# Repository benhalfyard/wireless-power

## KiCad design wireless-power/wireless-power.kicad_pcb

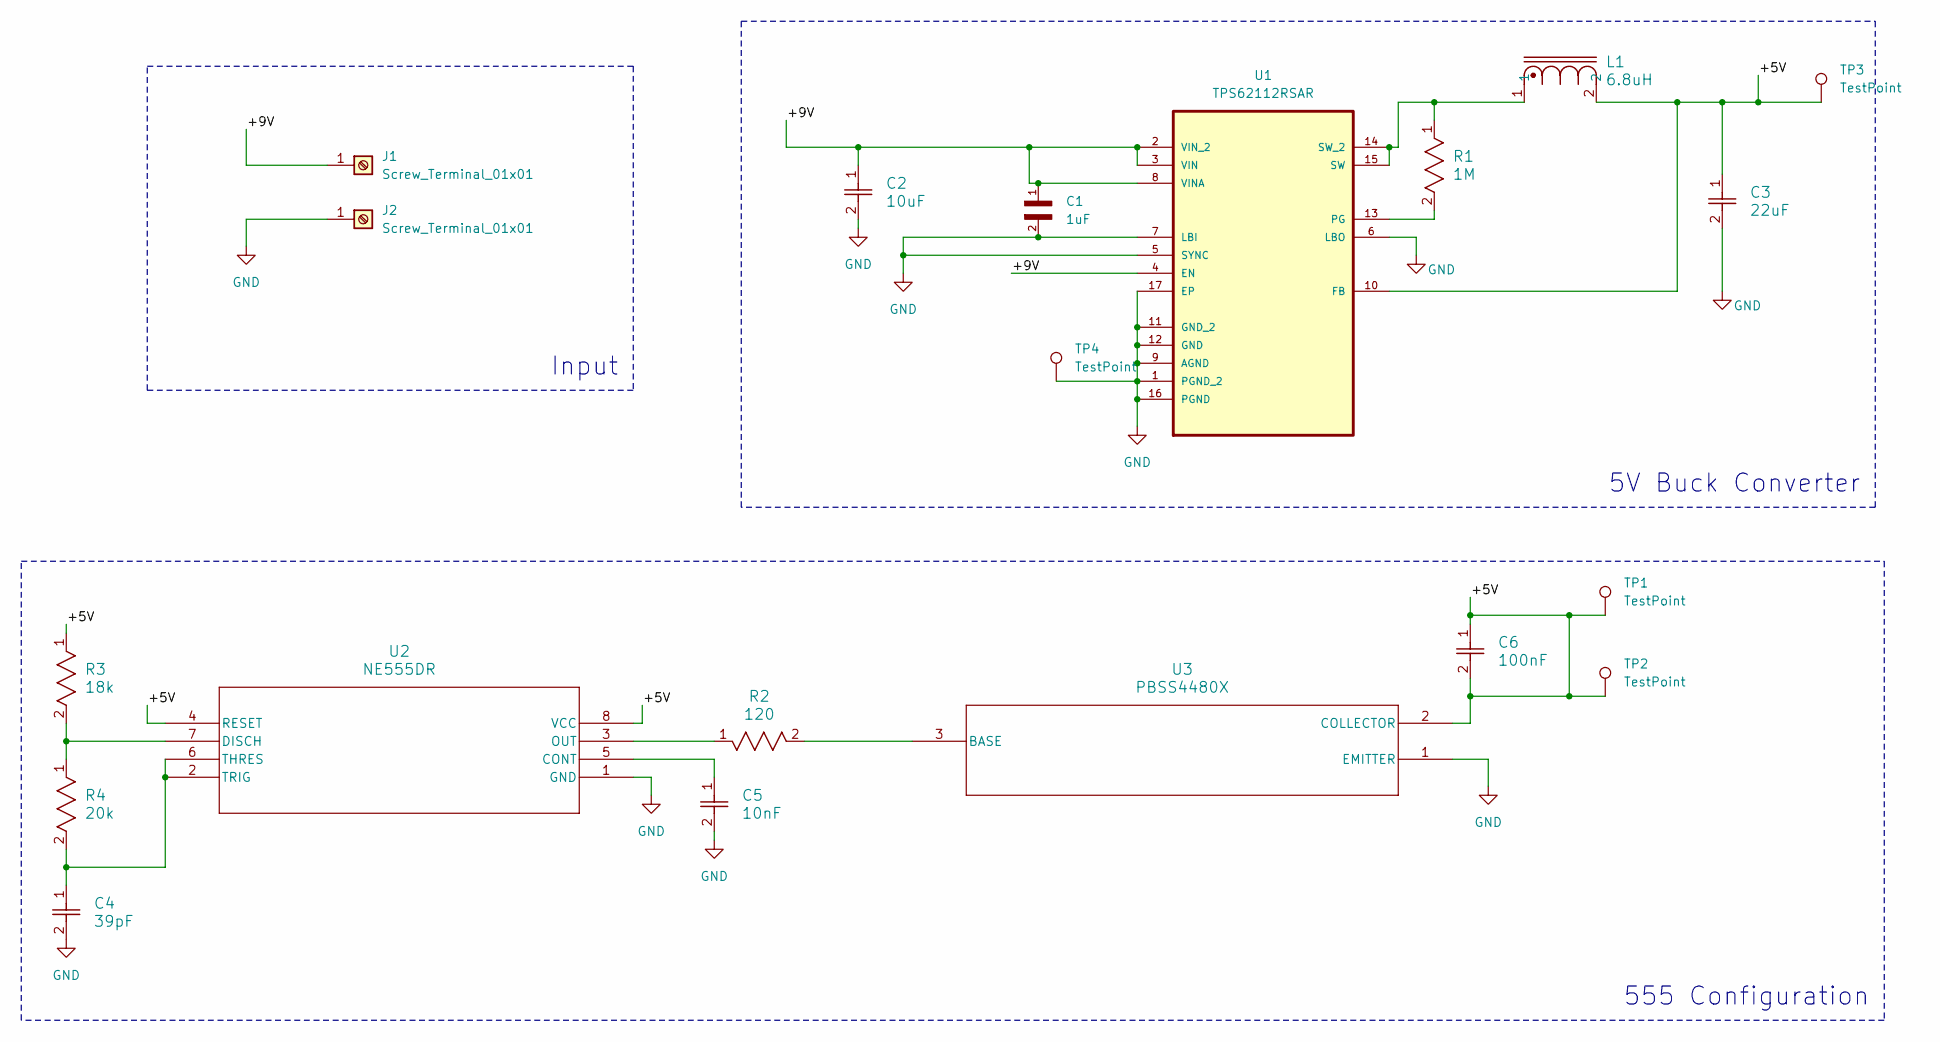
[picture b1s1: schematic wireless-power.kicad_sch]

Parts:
C1: 1uF; CAPC2012X135N
C2: 10uF; CAP_C3225-250_TDK
C3: 22uF; CAP_C3225-250_TDK
C4: 39pF; CAPC6333_33N_KEM
C5: 10nF; G-155_MUR
C6: 100nF; G-033_MUR
J1, J2: Screw_Terminal_01x01; TestPoint_Keystone_5019_Minature
L1: 6.8uH; DR125
R1: 1M; RC0603N_YAG
R2: 120; RC0603N_PAN
R3: 18k; RC0603N_YAG
R4: 20k; RC0402N_YAG
TP1, TP2, TP3, TP4: TestPoint; TestPoint_THTPad_1.0x1.0mm_Drill0.5mm
U1: TPS62112RSAR; QFN65P400X400X100-17N; MPN TPS62112RSAR
U2: NE555DR; D8
U3: PBSS4480X; SOT89_NXP

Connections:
/+5V: C3.1, C6.1, C6.2, L1.2, R3.1, TP1.1, TP2.1, TP3.1, U1.10 (FB), U2.4 (RESET), U2.8 (VCC), U3.2 (COLLECTOR)
/+9V: C1.1, C2.1, J1.1, U1.2 (VIN_2), U1.3 (VIN), U1.4 (EN), U1.8 (VINA)
GND: C1.2, C2.2, C3.2, C4.2, C5.2, J2.1, TP4.1, U1.1 (PGND_2), U1.5 (SYNC), U1.6 (LBO), U1.7 (LBI), U1.9 (AGND), U1.11 (GND_2), U1.12 (GND), U1.16 (PGND), U1.17 (EP), U2.1 (GND), U3.1 (EMITTER)
unnamed: R1.2, U1.13 (PG)
unnamed: L1.1, R1.1, U1.14 (SW_2), U1.15 (SW)
unnamed: C5.1, U2.5 (CONT)
unnamed: R3.2, R4.1, U2.7 (DISCH)
unnamed: R2.1, U2.3 (OUT)
unnamed: C4.1, R4.2, U2.2 (TRIG), U2.6 (THRES)
unnamed: R2.2, U3.3 (BASE)

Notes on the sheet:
Input
555 Configuration
5V Buck Converter

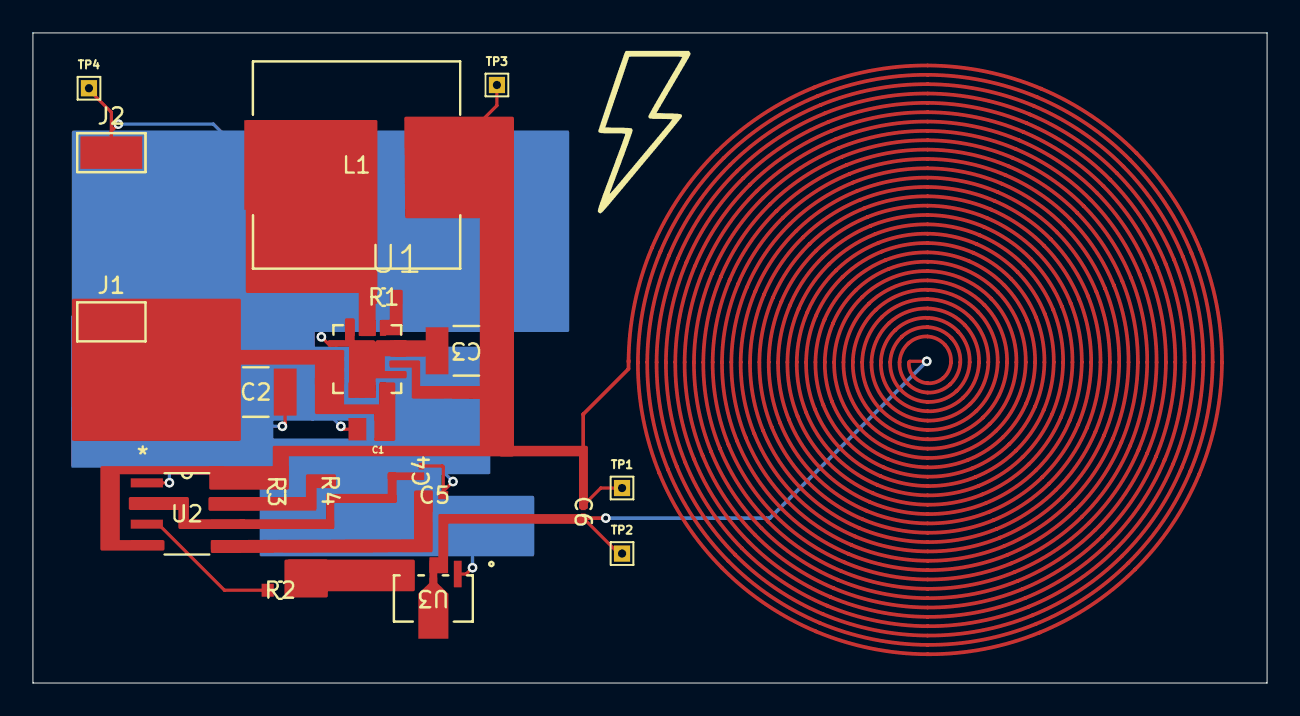
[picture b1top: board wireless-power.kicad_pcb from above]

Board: 2 copper layers, 75.9 x 40.0 mm, 20 parts (0 on the bottom side), 10 nets.

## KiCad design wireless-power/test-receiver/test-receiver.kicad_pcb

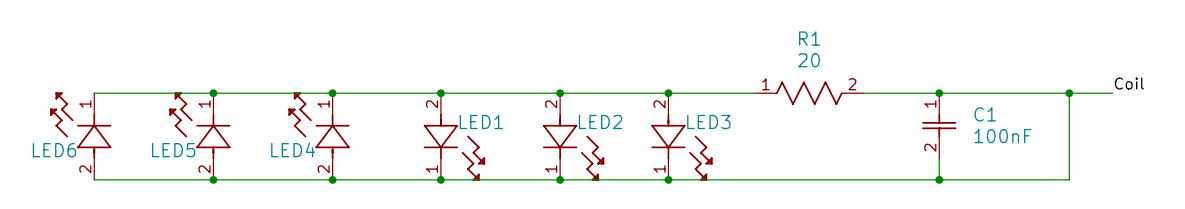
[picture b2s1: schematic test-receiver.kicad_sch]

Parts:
C1: 100nF; G-033_MUR
LED1, LED2, LED3, LED4, LED5, LED6: 151034BS03000; LED_BS03000_WRE
R1: 20; RES_R1632_ROM

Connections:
/Coil: C1.1, C1.2, LED1.1, LED2.1, LED3.1, LED4.2, LED5.2, LED6.2, R1.2
unnamed: LED1.2, LED2.2, LED3.2, LED4.1, LED5.1, LED6.1, R1.1

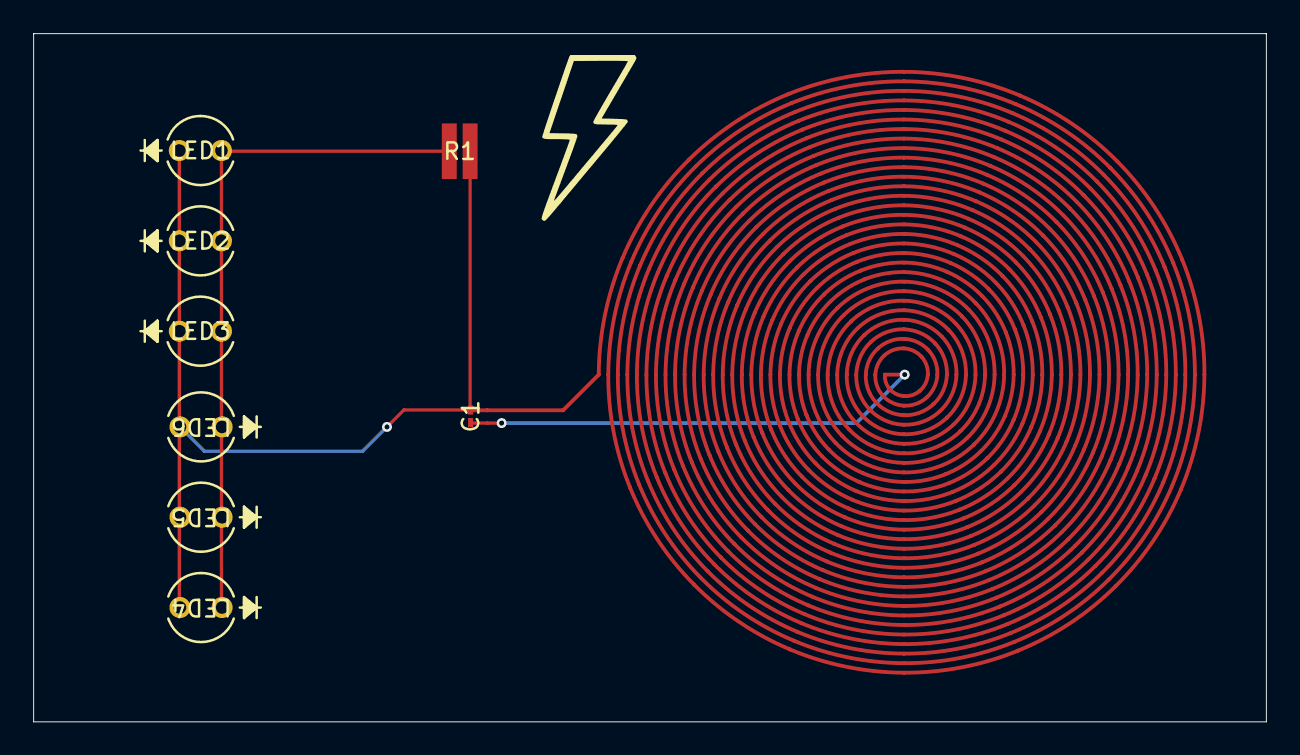
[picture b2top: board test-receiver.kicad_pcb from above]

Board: 2 copper layers, 74.3 x 41.5 mm, 8 parts (0 on the bottom side), 2 nets.

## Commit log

2024-03-22 project creation
2024-03-22 Buck Converter Design
2024-03-24 transistor
2024-03-24 imported schematic
2024-03-24 preliminary layout
2024-03-25 routed traces
2024-03-25 silkscreen
2024-03-26 changed coil terminal
2024-03-26 finalized transmitter PCB
2024-03-26 created receiver project
2024-03-27 finished receiver test board
2024-03-27 gerbers
2024-03-27 receiver gerber
2024-03-27 updated buck converter
2024-03-29 3d model
